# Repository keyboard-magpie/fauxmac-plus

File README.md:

# fauxmac-plus

Pin compatible with the thing that sounds a bit like this.
Same functions- oled, encoder- added breakouts/test points on rows and columns, and added battery/switch positions in case you want to wireless convert it.

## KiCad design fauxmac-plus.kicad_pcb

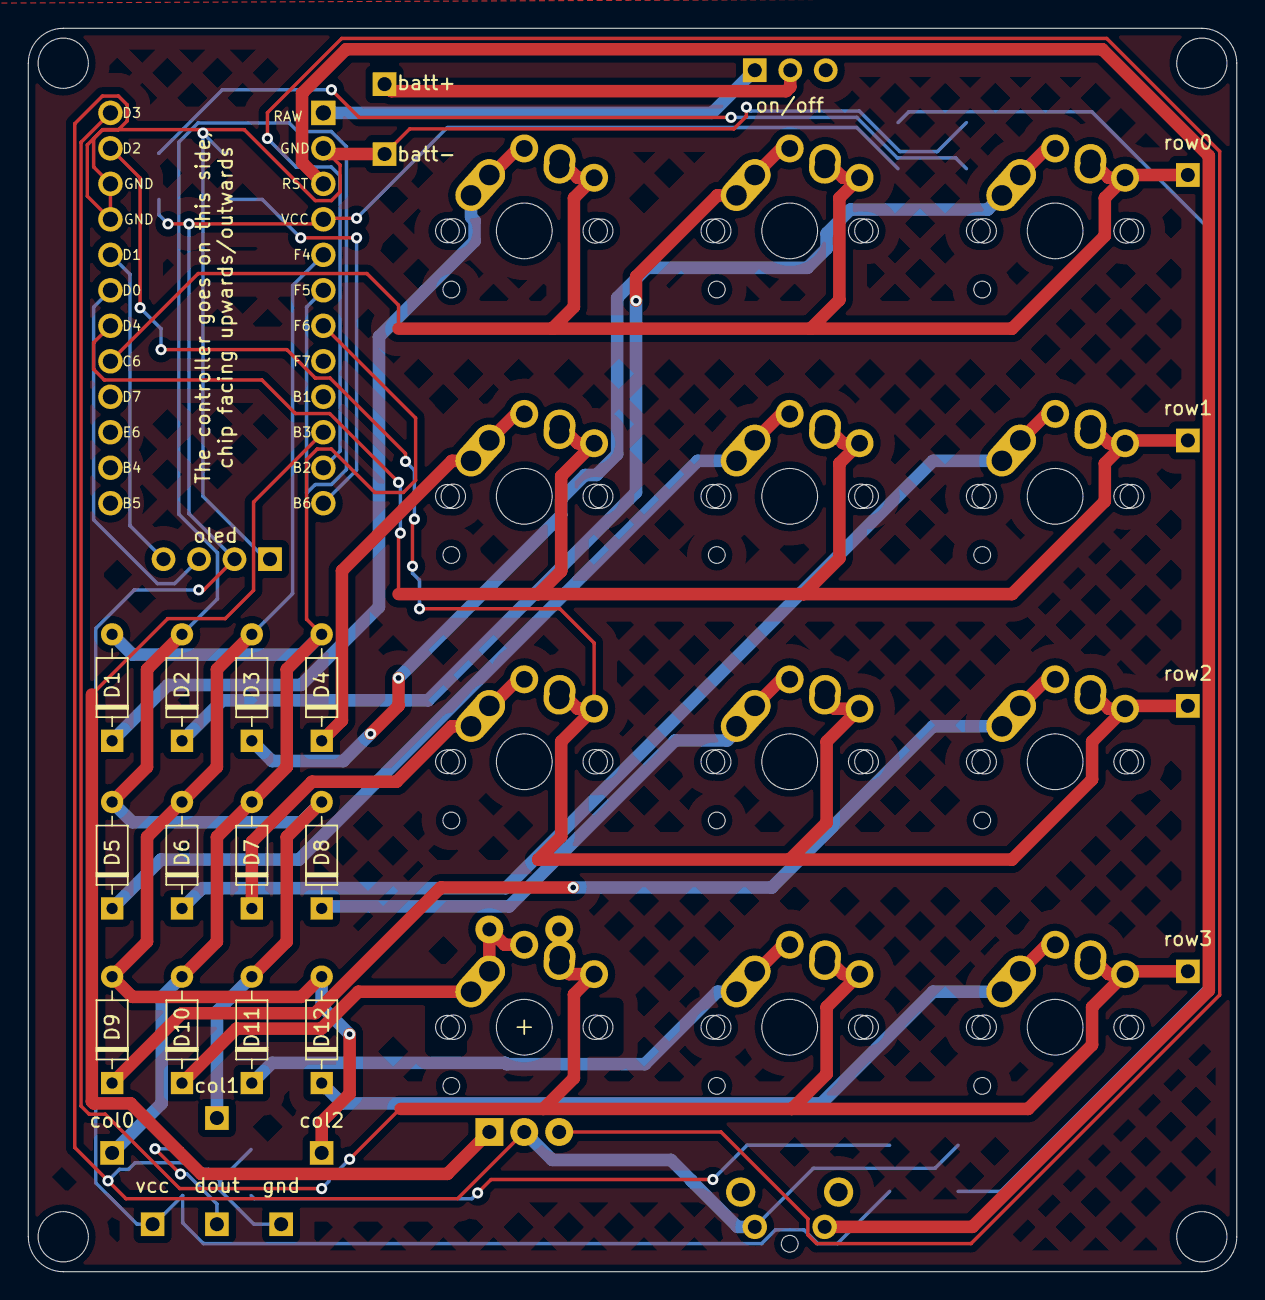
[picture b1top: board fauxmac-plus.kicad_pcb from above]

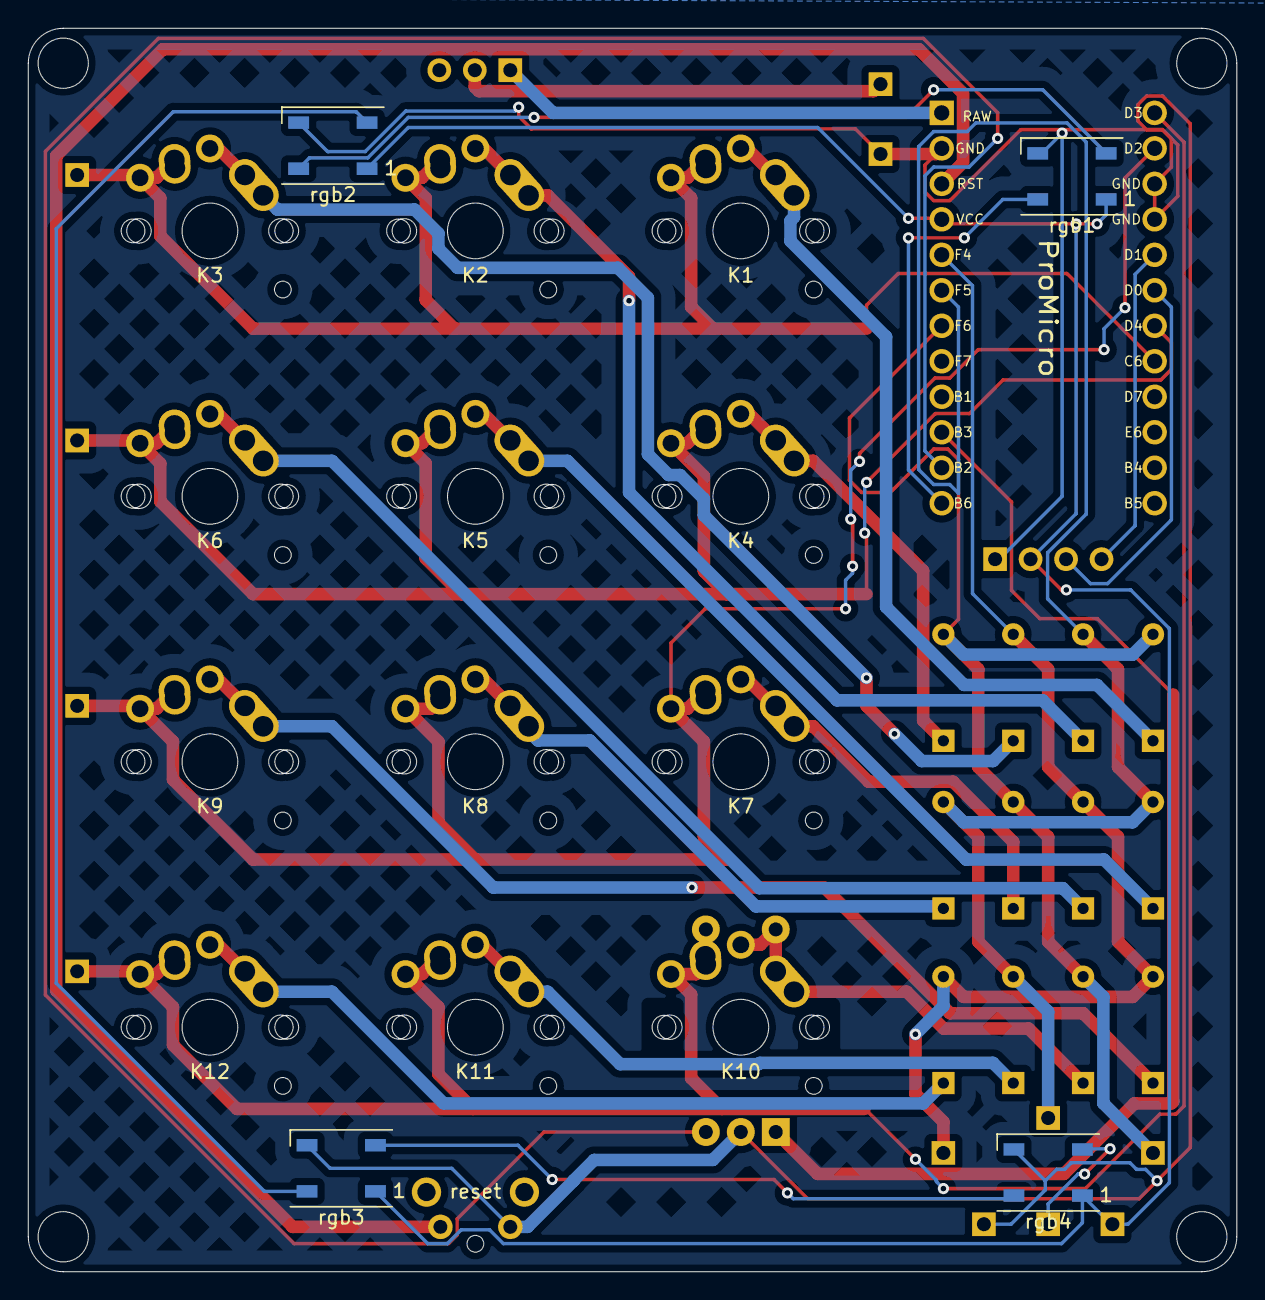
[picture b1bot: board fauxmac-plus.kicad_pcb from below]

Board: 2 copper layers, 86.5 x 89.0 mm, 45 parts (5 on the bottom side), 33 nets.

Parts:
D1, D2, D3, D4, D5, D6, D7, D8, D9, D10, D11, D12: 1N4148; D_DO-35_SOD27_P7.62mm_Horizontal
K1, K2, K3, K4, K5, K6, K7, K8, K9, K10, K11, K12: KEYSW; MX-Alps-Choc-1U-NoLED
U1: ProMicro; Pro_Micro
batt+: TestPoint; PinSocket_1x01_P2.54mm_Vertical
batt-: TestPoint; PinSocket_1x01_P2.54mm_Vertical
col0, col1, col2: Conn_01x01_Male; PinHeader_1x01_P2.54mm_Vertical
dout: TestPoint; PinSocket_1x01_P2.54mm_Vertical
enc1: Rotary_Encoder_Switch; RotaryEncoder_EC11
gnd: TestPoint; PinSocket_1x01_P2.54mm_Vertical
oled: oled; PinHeader_1x04_P2.54mm_Vertical
on/off: SW_DIP_x01; PinHeader_1x03_P2.54mm_Vertical
reset: SW_PUSH; SW_Tactile_SPST_Angled_MJTP1117
rgb1, rgb2, rgb3, rgb4: WS2812B; LED_WS2812B_PLCC4_5.0x5.0mm_P3.2mm
row0, row1, row2, row3: Conn_01x01_Male; PinHeader_1x01_P2.54mm_Vertical
vcc: TestPoint; PinSocket_1x01_P2.54mm_Vertical

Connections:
GND: U1.2 (GND), U1.15 (GND), U1.16 (GND), batt-.1, enc1.C, gnd.1, oled.1, reset.2, rgb1.3 (VSS), rgb2.3 (VSS), rgb3.3 (VSS), rgb4.3 (VSS)
unnamed: D1.1 (K), K1.2
unnamed: D2.1 (K), K2.2
unnamed: D3.1 (K), K3.2
unnamed: D4.1 (K), K4.2
unnamed: D5.1 (K), K5.2
unnamed: D6.1 (K), K6.2
unnamed: D7.1 (K), K7.2
unnamed: D8.1 (K), K8.2
unnamed: D9.1 (K), K9.2
unnamed: D10.1 (K), K10.2, enc1.S2
unnamed: D11.1 (K), K11.2
unnamed: D12.1 (K), K12.2
unnamed: U1.1 (RAW), on/off.1
unnamed: batt+.1, on/off.2
unnamed: rgb1.2 (DOUT), rgb2.4 (DIN)
unnamed: rgb2.2 (DOUT), rgb3.4 (DIN)
unnamed: rgb3.2 (DOUT), rgb4.4 (DIN)
unnamed: dout.1, rgb4.2 (DOUT)
VCC: U1.4 (VCC), oled.2, rgb1.1 (VDD), rgb2.1 (VDD), rgb3.1 (VDD), rgb4.1 (VDD), vcc.1
col0: D1.2 (A), D4.2 (A), D7.2 (A), D10.2 (A), U1.7 (PF6), col0.1
col1: D2.2 (A), D5.2 (A), D8.2 (A), D11.2 (A), U1.6 (PF5), col1.1
col2: D3.2 (A), D6.2 (A), D9.2 (A), D12.2 (A), U1.5 (PF4), col2.1
encA: U1.10 (PB3), enc1.A
encB: U1.11 (PB2), enc1.B
rgb: U1.12 (PB6), rgb1.4 (DIN)
row0: K1.1, K2.1, K3.1, U1.20 (PC6), row0.1
row1: K4.1, K5.1, K6.1, U1.19 (PD4), row1.1
row2: K7.1, K8.1, K9.1, U1.14 (PD2), row2.1
row3: K10.1, K11.1, K12.1, U1.13 (PD3), enc1.S1, row3.1
rst: U1.3 (RST), reset.1
scl: U1.18 (PD0), oled.3
sda: U1.17 (PD1), oled.4

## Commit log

2023-01-13 2023 updates to PCB with RGB and plates
2023-01-20 update mounting points, fix plate
2023-01-20 correct gerber issues
2023-01-20 amend oled labelling, regen gerbers
2023-02-16 v3 fauxmac updates- mounting holes altered on PCB, plate changes for reset switch and controller interference
2023-05-06 temp firmware additions
